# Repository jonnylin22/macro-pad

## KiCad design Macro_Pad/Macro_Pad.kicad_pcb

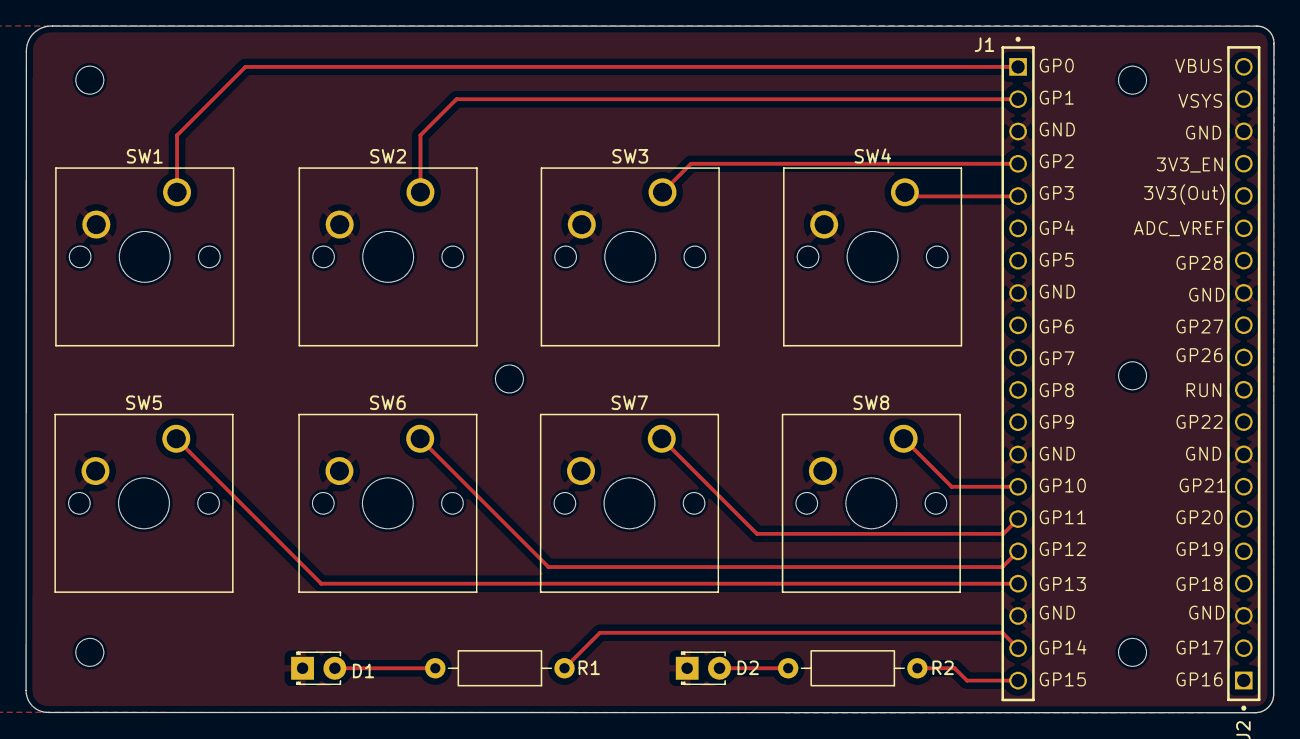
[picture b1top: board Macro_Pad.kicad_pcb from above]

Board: 2 copper layers, 98.1 x 54.0 mm, 14 parts (0 on the bottom side), 13 nets.

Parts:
D1, D2: LED; LED_D1.8mm_W3.3mm_H2.4mm
J1, J2: SSW-120-01-G-S-LL; SAMTEC_SSW-120-01-G-S-LL
R1, R2: 220; R_Axial_DIN0207_L6.3mm_D2.5mm_P10.16mm_Horizontal
SW1, SW2, SW3, SW4, SW5, SW6, SW7, SW8: CherryMX; SW_Cherry_MX_1.00u_PCB

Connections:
/GP0: J1.01, SW1.1
/GP1: J1.02, SW2.1
/GP2: J1.04, SW3.1
/GP3: J1.05, SW4.1
/GP10: J1.14, SW8.1
/GP11: J1.15, SW7.1
/GP12: J1.16, SW6.1
/GP13: J1.17, SW5.1
/GP14: J1.19, R1.1
/GP15: J1.20, R2.1
GND: D1.1 (K), D2.1 (K), J1.03, J1.08, J1.13, J1.18, J2.03, J2.08, J2.13, J2.18, SW1.2, SW2.2, SW3.2, SW4.2, SW5.2, SW6.2, SW7.2, SW8.2
unnamed: D1.2 (A), R1.2
unnamed: D2.2 (A), R2.2

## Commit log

2025-09-20 macro pad v2 with gerbers
2025-09-21 macro pad v3 smaller < 100x100 mm size + gerbers
